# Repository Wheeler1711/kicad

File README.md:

# kicad
Jordan Wheeler PCBs files

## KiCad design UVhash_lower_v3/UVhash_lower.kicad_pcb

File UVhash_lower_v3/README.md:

## PCB file to make a breakout for 25 pin mico-D 

Also, there is DXF for a send cut send bracket to hold the PCB in the cyostat. Designed for 4-40 tapped holes

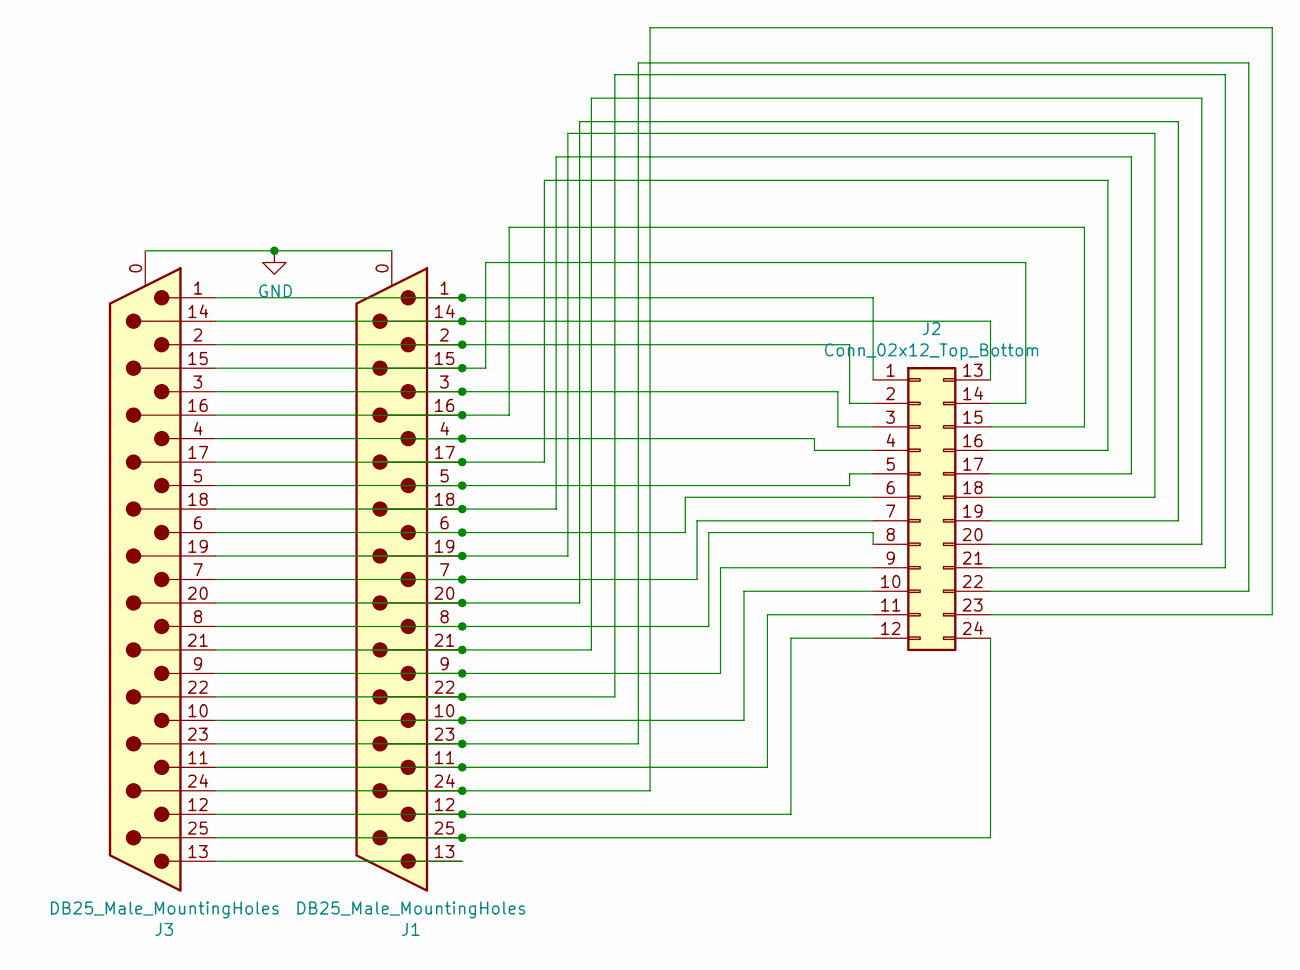
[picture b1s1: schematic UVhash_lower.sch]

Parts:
J1, J3: DB25_Male_MountingHoles; 25_pin_micro_D_male_straight_mount_pdb_wide_spacing
J2: Conn_02x12_Top_Bottom; PinSocket_2x12_P2.54mm_Vertical_twisted_pair

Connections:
GND: J1.0 (PAD), J3.0 (PAD)
unnamed: J1.1, J2.1, J3.1
unnamed: J1.2, J2.2, J3.2
unnamed: J1.3, J2.3, J3.3
unnamed: J1.4, J2.4, J3.4
unnamed: J1.5, J2.5, J3.5
unnamed: J1.6, J2.6, J3.6
unnamed: J1.7, J2.7, J3.7
unnamed: J1.8, J2.8, J3.8
unnamed: J1.9, J2.9, J3.9
unnamed: J1.10, J2.10, J3.10
unnamed: J1.11, J2.11, J3.11
unnamed: J1.12, J2.12, J3.12
unnamed: J1.13, J3.13
unnamed: J1.14, J2.13, J3.14
unnamed: J1.15, J2.14, J3.15
unnamed: J1.16, J2.15, J3.16
unnamed: J1.17, J2.16, J3.17
unnamed: J1.18, J2.17, J3.18
unnamed: J1.19, J2.18, J3.19
unnamed: J1.20, J2.19, J3.20
unnamed: J1.21, J2.20, J3.21
unnamed: J1.22, J2.21, J3.22
unnamed: J1.23, J2.22, J3.23
unnamed: J1.24, J2.23, J3.24
unnamed: J1.25, J2.24, J3.25

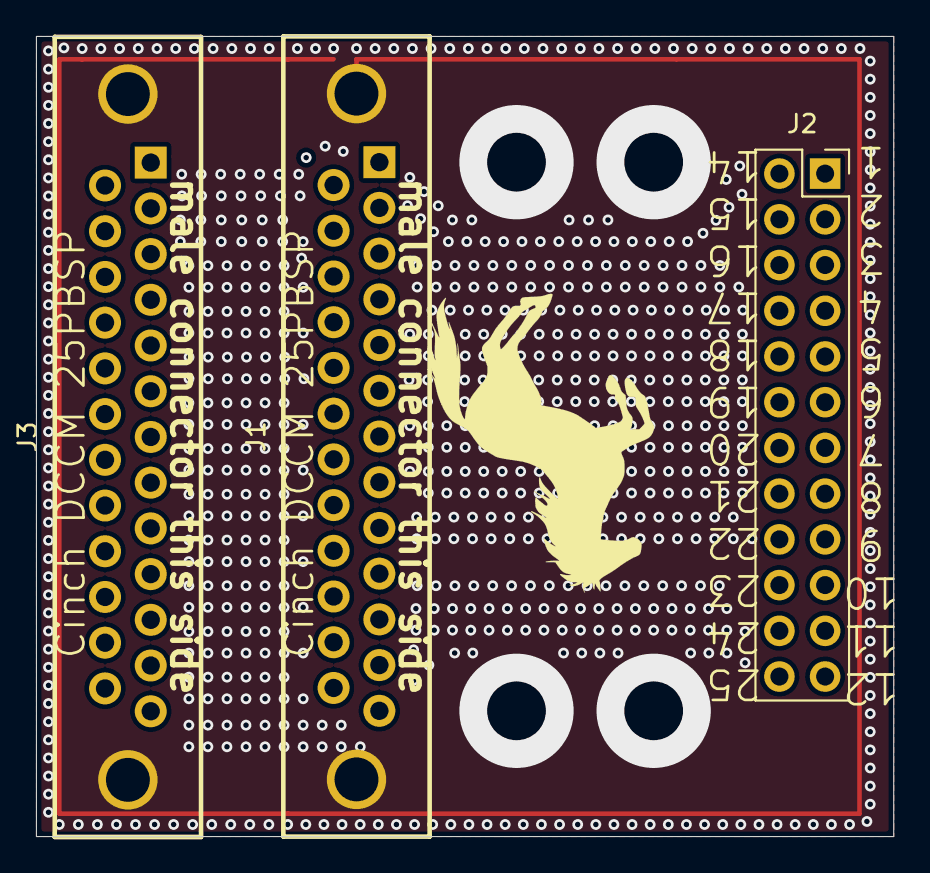
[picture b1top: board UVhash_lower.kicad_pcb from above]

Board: 4 copper layers, 47.6 x 44.5 mm, 3 parts (0 on the bottom side), 26 nets.

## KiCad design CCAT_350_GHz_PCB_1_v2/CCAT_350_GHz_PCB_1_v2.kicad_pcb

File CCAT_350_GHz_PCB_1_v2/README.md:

## PCB file for interface to 350 GHz CCAT arrays

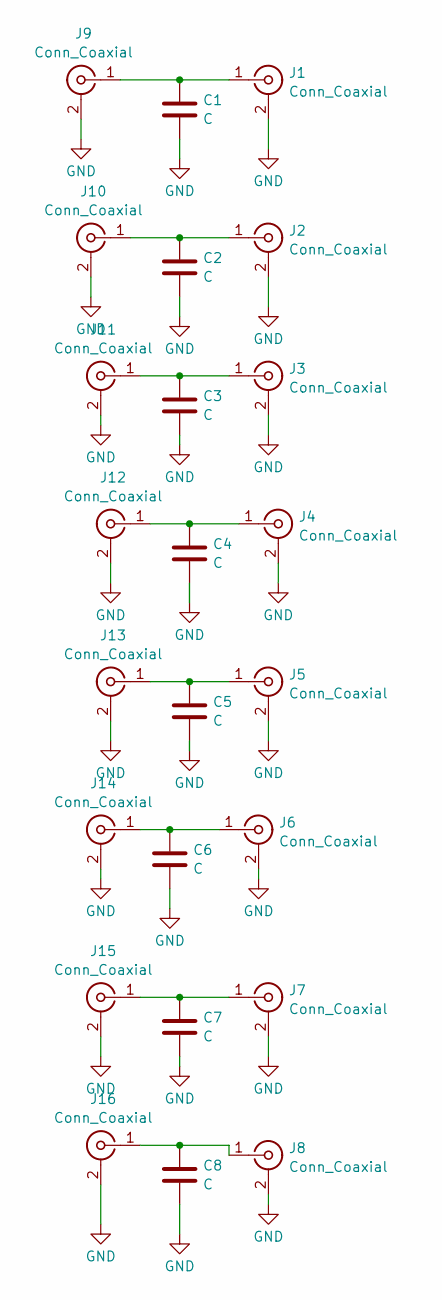
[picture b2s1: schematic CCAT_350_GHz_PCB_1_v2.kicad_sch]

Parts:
C1, C2, C3, C4, C5, C6, C7, C8: C; C_0402_1005Metric
J1, J2, J3, J4, J5, J6, J7, J8: Conn_Coaxial; coax_solder_cpw_44_trace_50_gap_rogers4350B_20_mil_thick
J9, J10, J11, J12, J13, J14, J15, J16: Conn_Coaxial; cpw_18_trace_4_gap_rogers_4350B_20_mil_thick

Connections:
GND: C1.2, C2.2, C3.2, C4.2, C5.2, C6.2, C7.2, C8.2, J1.2 (Ext), J2.2 (Ext), J3.2 (Ext), J4.2 (Ext), J5.2 (Ext), J6.2 (Ext), J7.2 (Ext), J8.2 (Ext), J9.2 (Ext), J10.2 (Ext), J11.2 (Ext), J12.2 (Ext), J13.2 (Ext), J14.2 (Ext), J15.2 (Ext), J16.2 (Ext)
unnamed: C1.1, J1.1 (In), J9.1 (In)
unnamed: C2.1, J2.1 (In), J10.1 (In)
unnamed: C3.1, J3.1 (In), J11.1 (In)
unnamed: C4.1, J4.1 (In), J12.1 (In)
unnamed: C5.1, J5.1 (In), J13.1 (In)
unnamed: C6.1, J6.1 (In), J14.1 (In)
unnamed: C7.1, J7.1 (In), J15.1 (In)
unnamed: C8.1, J8.1 (In), J16.1 (In)

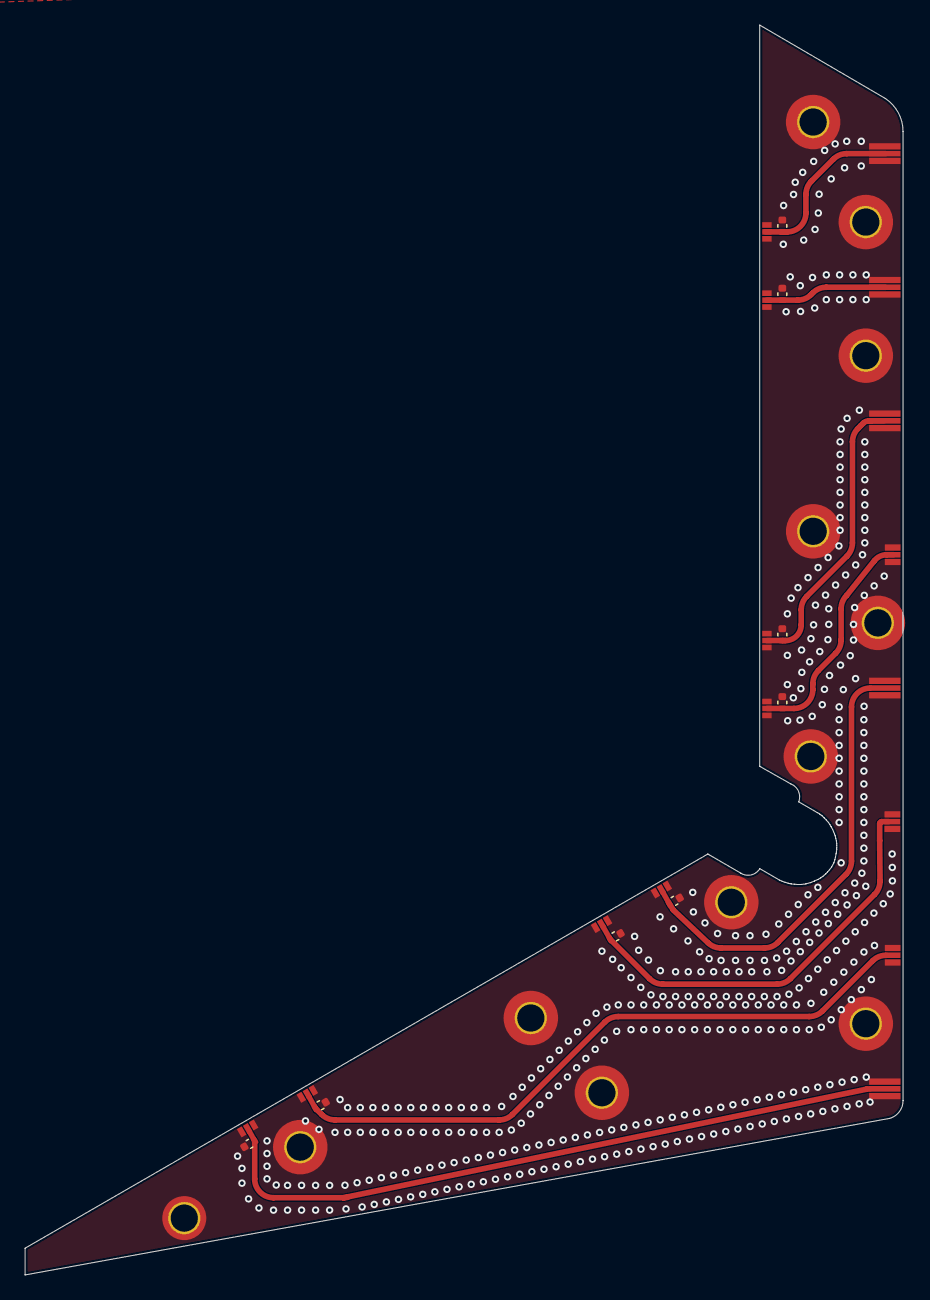
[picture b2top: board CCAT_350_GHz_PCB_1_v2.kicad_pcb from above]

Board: 2 copper layers, 70.9 x 101.0 mm, 24 parts (0 on the bottom side), 9 nets.

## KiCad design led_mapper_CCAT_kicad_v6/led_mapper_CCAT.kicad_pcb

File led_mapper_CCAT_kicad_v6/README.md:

## PCB file to led mapper for CCAT arrays

This is basically two arrays of charlieplexed leds

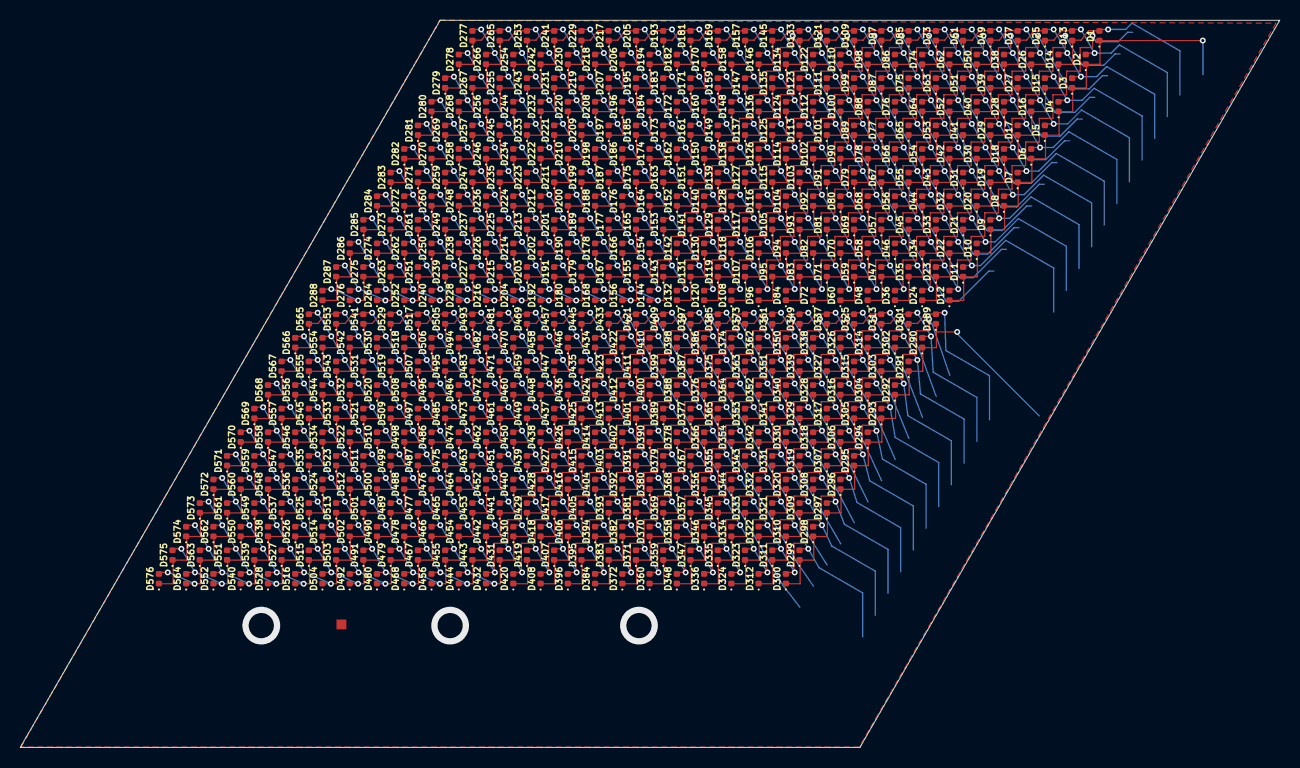
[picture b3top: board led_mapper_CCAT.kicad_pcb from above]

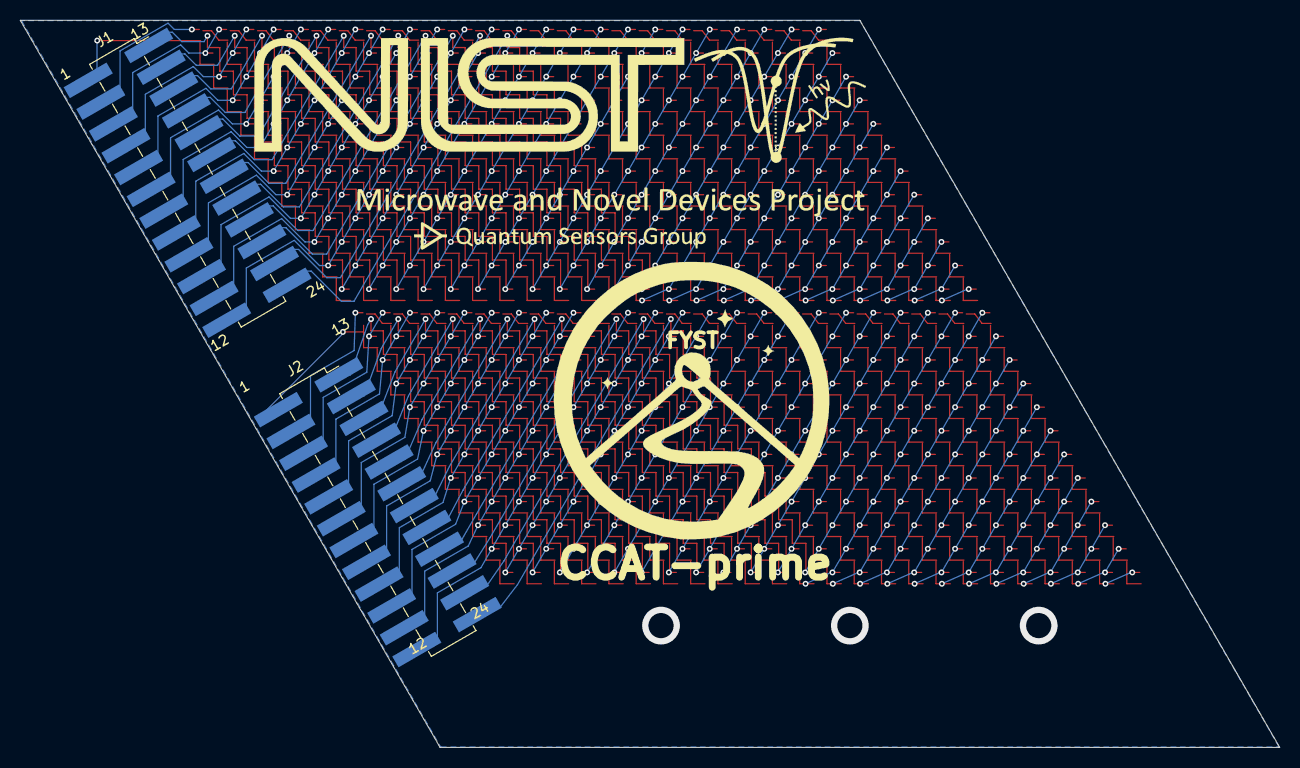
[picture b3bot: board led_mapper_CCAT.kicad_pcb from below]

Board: 2 copper layers, 127.0 x 73.4 mm, 579 parts (2 on the bottom side), 48 nets.

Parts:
D1, D2, D3, D4, D5, D6, D7, D8, D9, D10, D11, D12, D13, D14, D15, D16, D17, D18, D19, D20, D21, D22, D23, D24, D25, D26, D27, D28, D29, D30, D31, D32, D33, D34, D35, D36, D37, D38, D39, D40, D41, D42, D43, D44, D45, D46, D47, D48, D49, D50, D51, D52, D53, D54, D55, D56, D57, D58, D59, D60, D61, D62, D63, D64, D65, D66, D67, D68, D69, D70, D71, D72, D73, D74, D75, D76, D77, D78, D79, D80, D81, D82, D83, D84, D85, D86, D87, D88, D89, D90, D91, D92, D93, D94, D95, D96, D97, D98, D99, D100, D101, D102, D103, D104, D105, D106, D107, D108, D109, D110, D111, D112, D113, D114, D115, D116, D117, D118, D119, D120, D121, D122, D123, D124, D125, D126, D127, D128, D129, D130, D131, D132, D133, D134, D135, D136, D137, D138, D139, D140, D141, D142, D143, D144, D145, D146, D147, D148, D149, D150, D151, D152, D153, D154, D155, D156, D157, D158, D159, D160, D161, D162, D163, D164, D165, D166, D167, D168, D169, D170, D171, D172, D173, D174, D175, D176, D177, D178, D179, D180, D181, D182, D183, D184, D185, D186, D187, D188, D189, D190, D191, D192, D193, D194, D195, D196, D197, D198, D199, D200, D201, D202, D203, D204, D205, D206, D207, D208, D209, D210, D211, D212, D213, D214, D215, D216, D217, D218, D219, D220, D221, D222, D223, D224, D225, D226, D227, D228, D229, D230, D231, D232, D233, D234, D235, D236, D237, D238, D239, D240, D241, D242, D243, D244, D245, D246, D247, D248, D249, D250, D251, D252, D253, D254, D255, D256, D257, D258, D259, D260, D261, D262, D263, D264, D265, D266, D267, D268, D269, D270, D271, D272, D273, D274, D275, D276, D277, D278, D279, D280, D281, D282, D283, D284, D285, D286, D287, D288, D289, D290, D291, D292, D293, D294, D295, D296, D297, D298, D299, D300, D301, D302, D303, D304, D305, D306, D307, D308, D309, D310, D311, D312, D313, D314, D315, D316, D317, D318, D319, D320, D321, D322, D323, D324, D325, D326, D327, D328, D329, D330, D331, D332, D333, D334, D335, D336, D337, D338, D339, D340, D341, D342, D343, D344, D345, D346, D347, D348, D349, D350, D351, D352, D353, D354, D355, D356, D357, D358, D359, D360, D361, D362, D363, D364, D365, D366, D367, D368, D369, D370, D371, D372, D373, D374, D375, D376, D377, D378, D379, D380, D381, D382, D383, D384, D385, D386, D387, D388, D389, D390, D391, D392, D393, D394, D395, D396, D397, D398, D399, D400, D401, D402, D403, D404, D405, D406, D407, D408, D409, D410, D411, D412, D413, D414, D415, D416, D417, D418, D419, D420, D421, D422, D423, D424, D425, D426, D427, D428, D429, D430, D431, D432, D433, D434, D435, D436, D437, D438, D439, D440, D441, D442, D443, D444, D445, D446, D447, D448, D449, D450, D451, D452, D453, D454, D455, D456, D457, D458, D459, D460, D461, D462, D463, D464, D465, D466, D467, D468, D469, D470, D471, D472, D473, D474, D475, D476, D477, D478, D479, D480, D481, D482, D483, D484, D485, D486, D487, D488, D489, D490, D491, D492, D493, D494, D495, D496, D497, D498, D499, D500, D501, D502, D503, D504, D505, D506, D507, D508, D509, D510, D511, D512, D513, D514, D515, D516, D517, D518, D519, D520, D521, D522, D523, D524, D525, D526, D527, D528, D529, D530, D531, D532, D533, D534, D535, D536, D537, D538, D539, D540, D541, D542, D543, D544, D545, D546, D547, D548, D549, D550, D551, D552, D553, D554, D555, D556, D557, D558, D559, D560, D561, D562, D563, D564, D565, D566, D567, D568, D569, D570, D571, D572, D573, D574, D575, D576: LED; LED_0402_1005Metric
J1, J2: Conn_02x12_Top_Bottom; PinSocket_2x12_P2.54mm_Vertical_SMD_custom
J3: Conn_01x01_Female; TestPoint_Pad_1.0x1.0mm

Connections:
/pin1: D1.1, D2.1, D3.1, D4.1, D5.1, D6.1, D7.1, D8.1, D9.1, D10.1, D11.1, D12.1, J1.1
/pin1_b: D289.1, D290.1, D291.1, D292.1, D293.1, D294.1, D295.1, D296.1, D297.1, D298.1, D299.1, D300.1, J2.1
/pin2: D1.2, D13.1, D14.1, D15.1, D16.1, D17.1, D18.1, D19.1, D20.1, D21.1, D22.1, D23.1, D24.1, J1.2
/pin2_b: D289.2, D301.1, D302.1, D303.1, D304.1, D305.1, D306.1, D307.1, D308.1, D309.1, D310.1, D311.1, D312.1, J2.2
/pin3: D2.2, D13.2, D25.1, D26.1, D27.1, D28.1, D29.1, D30.1, D31.1, D32.1, D33.1, D34.1, D35.1, D36.1, J1.3
/pin3_b: D290.2, D301.2, D313.1, D314.1, D315.1, D316.1, D317.1, D318.1, D319.1, D320.1, D321.1, D322.1, D323.1, D324.1, J2.3
/pin4: D3.2, D14.2, D25.2, D37.1, D38.1, D39.1, D40.1, D41.1, D42.1, D43.1, D44.1, D45.1, D46.1, D47.1, D48.1, J1.4
/pin4_b: D291.2, D302.2, D313.2, D325.1, D326.1, D327.1, D328.1, D329.1, D330.1, D331.1, D332.1, D333.1, D334.1, D335.1, D336.1, J2.4
/pin5: D4.2, D15.2, D26.2, D37.2, D49.1, D50.1, D51.1, D52.1, D53.1, D54.1, D55.1, D56.1, D57.1, D58.1, D59.1, D60.1, J1.5
/pin5_b: D292.2, D303.2, D314.2, D325.2, D337.1, D338.1, D339.1, D340.1, D341.1, D342.1, D343.1, D344.1, D345.1, D346.1, D347.1, D348.1, J2.5
/pin6: D5.2, D16.2, D27.2, D38.2, D49.2, D61.1, D62.1, D63.1, D64.1, D65.1, D66.1, D67.1, D68.1, D69.1, D70.1, D71.1, D72.1, J1.6
/pin6_b: D293.2, D304.2, D315.2, D326.2, D337.2, D349.1, D350.1, D351.1, D352.1, D353.1, D354.1, D355.1, D356.1, D357.1, D358.1, D359.1, D360.1, J2.6
/pin7: D6.2, D17.2, D28.2, D39.2, D50.2, D61.2, D73.1, D74.1, D75.1, D76.1, D77.1, D78.1, D79.1, D80.1, D81.1, D82.1, D83.1, D84.1, J1.7
/pin7_b: D294.2, D305.2, D316.2, D327.2, D338.2, D349.2, D361.1, D362.1, D363.1, D364.1, D365.1, D366.1, D367.1, D368.1, D369.1, D370.1, D371.1, D372.1, J2.7
/pin8: D7.2, D18.2, D29.2, D40.2, D51.2, D62.2, D73.2, D85.1, D86.1, D87.1, D88.1, D89.1, D90.1, D91.1, D92.1, D93.1, D94.1, D95.1, D96.1, J1.8
/pin8_b: D295.2, D306.2, D317.2, D328.2, D339.2, D350.2, D361.2, D373.1, D374.1, D375.1, D376.1, D377.1, D378.1, D379.1, D380.1, D381.1, D382.1, D383.1, D384.1, J2.8
/pin9: D8.2, D19.2, D30.2, D41.2, D52.2, D63.2, D74.2, D85.2, D97.1, D98.1, D99.1, D100.1, D101.1, D102.1, D103.1, D104.1, D105.1, D106.1, D107.1, D108.1, J1.9
/pin9_b: D296.2, D307.2, D318.2, D329.2, D340.2, D351.2, D362.2, D373.2, D385.1, D386.1, D387.1, D388.1, D389.1, D390.1, D391.1, D392.1, D393.1, D394.1, D395.1, D396.1, J2.9
/pin10: D9.2, D20.2, D31.2, D42.2, D53.2, D64.2, D75.2, D86.2, D97.2, D109.1, D110.1, D111.1, D112.1, D113.1, D114.1, D115.1, D116.1, D117.1, D118.1, D119.1, D120.1, J1.10
/pin10_b: D297.2, D308.2, D319.2, D330.2, D341.2, D352.2, D363.2, D374.2, D385.2, D397.1, D398.1, D399.1, D400.1, D401.1, D402.1, D403.1, D404.1, D405.1, D406.1, D407.1, D408.1, J2.10
/pin11: D10.2, D21.2, D32.2, D43.2, D54.2, D65.2, D76.2, D87.2, D98.2, D109.2, D121.1, D122.1, D123.1, D124.1, D125.1, D126.1, D127.1, D128.1, D129.1, D130.1, D131.1, D132.1, J1.11
/pin11_b: D298.2, D309.2, D320.2, D331.2, D342.2, D353.2, D364.2, D375.2, D386.2, D397.2, D409.1, D410.1, D411.1, D412.1, D413.1, D414.1, D415.1, D416.1, D417.1, D418.1, D419.1, D420.1, J2.11
/pin12: D11.2, D22.2, D33.2, D44.2, D55.2, D66.2, D77.2, D88.2, D99.2, D110.2, D121.2, D133.1, D134.1, D135.1, D136.1, D137.1, D138.1, D139.1, D140.1, D141.1, D142.1, D143.1, D144.1, D156.2, D167.2, D178.2, D189.2, D200.2, D211.2, D222.2, D233.2, D244.2, D255.2, D266.2, D277.2, J1.12
/pin12_b: D299.2, D310.2, D321.2, D332.2, D343.2, D354.2, D365.2, D376.2, D387.2, D398.2, D409.2, D421.1, D422.1, D423.1, D424.1, D425.1, D426.1, D427.1, D428.1, D429.1, D430.1, D431.1, D432.1, D444.2, D455.2, D466.2, D477.2, D488.2, D499.2, D510.2, D521.2, D532.2, D543.2, D554.2, D565.2, J2.12
/pin13: D12.2, D23.2, D34.2, D45.2, D56.2, D67.2, D78.2, D89.2, D100.2, D111.2, D122.2, D133.2, D145.1, D146.1, D147.1, D148.1, D149.1, D150.1, D151.1, D152.1, D153.1, D154.1, D155.1, D156.1, D168.2, D179.2, D190.2, D201.2, D212.2, D223.2, D234.2, D245.2, D256.2, D267.2, D278.2, J1.13
/pin13_b: D300.2, D311.2, D322.2, D333.2, D344.2, D355.2, D366.2, D377.2, D388.2, D399.2, D410.2, D421.2, D433.1, D434.1, D435.1, D436.1, D437.1, D438.1, D439.1, D440.1, D441.1, D442.1, D443.1, D444.1, D456.2, D467.2, D478.2, D489.2, D500.2, D511.2, D522.2, D533.2, D544.2, D555.2, D566.2, J2.13
/pin14: D24.2, D35.2, D46.2, D57.2, D68.2, D79.2, D90.2, D101.2, D112.2, D123.2, D134.2, D145.2, D157.1, D158.1, D159.1, D160.1, D161.1, D162.1, D163.1, D164.1, D165.1, D166.1, D167.1, D168.1, D180.2, D191.2, D202.2, D213.2, D224.2, D235.2, D246.2, D257.2, D268.2, D279.2, J1.14
/pin14_b: D312.2, D323.2, D334.2, D345.2, D356.2, D367.2, D378.2, D389.2, D400.2, D411.2, D422.2, D433.2, D445.1, D446.1, D447.1, D448.1, D449.1, D450.1, D451.1, D452.1, D453.1, D454.1, D455.1, D456.1, D468.2, D479.2, D490.2, D501.2, D512.2, D523.2, D534.2, D545.2, D556.2, D567.2, J2.14
/pin15: D36.2, D47.2, D58.2, D69.2, D80.2, D91.2, D102.2, D113.2, D124.2, D135.2, D146.2, D157.2, D169.1, D170.1, D171.1, D172.1, D173.1, D174.1, D175.1, D176.1, D177.1, D178.1, D179.1, D180.1, D192.2, D203.2, D214.2, D225.2, D236.2, D247.2, D258.2, D269.2, D280.2, J1.15
/pin15_b: D324.2, D335.2, D346.2, D357.2, D368.2, D379.2, D390.2, D401.2, D412.2, D423.2, D434.2, D445.2, D457.1, D458.1, D459.1, D460.1, D461.1, D462.1, D463.1, D464.1, D465.1, D466.1, D467.1, D468.1, D480.2, D491.2, D502.2, D513.2, D524.2, D535.2, D546.2, D557.2, D568.2, J2.15
/pin16: D48.2, D59.2, D70.2, D81.2, D92.2, D103.2, D114.2, D125.2, D136.2, D147.2, D158.2, D169.2, D181.1, D182.1, D183.1, D184.1, D185.1, D186.1, D187.1, D188.1, D189.1, D190.1, D191.1, D192.1, D204.2, D215.2, D226.2, D237.2, D248.2, D259.2, D270.2, D281.2, J1.16
/pin16_b: D336.2, D347.2, D358.2, D369.2, D380.2, D391.2, D402.2, D413.2, D424.2, D435.2, D446.2, D457.2, D469.1, D470.1, D471.1, D472.1, D473.1, D474.1, D475.1, D476.1, D477.1, D478.1, D479.1, D480.1, D492.2, D503.2, D514.2, D525.2, D536.2, D547.2, D558.2, D569.2, J2.16
/pin17: D60.2, D71.2, D82.2, D93.2, D104.2, D115.2, D126.2, D137.2, D148.2, D159.2, D170.2, D181.2, D193.1, D194.1, D195.1, D196.1, D197.1, D198.1, D199.1, D200.1, D201.1, D202.1, D203.1, D204.1, D216.2, D227.2, D238.2, D249.2, D260.2, D271.2, D282.2, J1.17
/pin17_b: D348.2, D359.2, D370.2, D381.2, D392.2, D403.2, D414.2, D425.2, D436.2, D447.2, D458.2, D469.2, D481.1, D482.1, D483.1, D484.1, D485.1, D486.1, D487.1, D488.1, D489.1, D490.1, D491.1, D492.1, D504.2, D515.2, D526.2, D537.2, D548.2, D559.2, D570.2, J2.17
/pin18: D72.2, D83.2, D94.2, D105.2, D116.2, D127.2, D138.2, D149.2, D160.2, D171.2, D182.2, D193.2, D205.1, D206.1, D207.1, D208.1, D209.1, D210.1, D211.1, D212.1, D213.1, D214.1, D215.1, D216.1, D228.2, D239.2, D250.2, D261.2, D272.2, D283.2, J1.18
/pin18_b: D360.2, D371.2, D382.2, D393.2, D404.2, D415.2, D426.2, D437.2, D448.2, D459.2, D470.2, D481.2, D493.1, D494.1, D495.1, D496.1, D497.1, D498.1, D499.1, D500.1, D501.1, D502.1, D503.1, D504.1, D516.2, D527.2, D538.2, D549.2, D560.2, D571.2, J2.18
/pin19: D84.2, D95.2, D106.2, D117.2, D128.2, D139.2, D150.2, D161.2, D172.2, D183.2, D194.2, D205.2, D217.1, D218.1, D219.1, D220.1, D221.1, D222.1, D223.1, D224.1, D225.1, D226.1, D227.1, D228.1, D240.2, D251.2, D262.2, D273.2, D284.2, J1.19
/pin19_b: D372.2, D383.2, D394.2, D405.2, D416.2, D427.2, D438.2, D449.2, D460.2, D471.2, D482.2, D493.2, D505.1, D506.1, D507.1, D508.1, D509.1, D510.1, D511.1, D512.1, D513.1, D514.1, D515.1, D516.1, D528.2, D539.2, D550.2, D561.2, D572.2, J2.19
/pin20: D96.2, D107.2, D118.2, D129.2, D140.2, D151.2, D162.2, D173.2, D184.2, D195.2, D206.2, D217.2, D229.1, D230.1, D231.1, D232.1, D233.1, D234.1, D235.1, D236.1, D237.1, D238.1, D239.1, D240.1, D252.2, D263.2, D274.2, D285.2, J1.20
/pin20_b: D384.2, D395.2, D406.2, D417.2, D428.2, D439.2, D450.2, D461.2, D472.2, D483.2, D494.2, D505.2, D517.1, D518.1, D519.1, D520.1, D521.1, D522.1, D523.1, D524.1, D525.1, D526.1, D527.1, D528.1, D540.2, D551.2, D562.2, D573.2, J2.20
/pin21: D108.2, D119.2, D130.2, D141.2, D152.2, D163.2, D174.2, D185.2, D196.2, D207.2, D218.2, D229.2, D241.1, D242.1, D243.1, D244.1, D245.1, D246.1, D247.1, D248.1, D249.1, D250.1, D251.1, D252.1, D264.2, D275.2, D286.2, J1.21
/pin21_b: D396.2, D407.2, D418.2, D429.2, D440.2, D451.2, D462.2, D473.2, D484.2, D495.2, D506.2, D517.2, D529.1, D530.1, D531.1, D532.1, D533.1, D534.1, D535.1, D536.1, D537.1, D538.1, D539.1, D540.1, D552.2, D563.2, D574.2, J2.21
/pin22: D120.2, D131.2, D142.2, D153.2, D164.2, D175.2, D186.2, D197.2, D208.2, D219.2, D230.2, D241.2, D253.1, D254.1, D255.1, D256.1, D257.1, D258.1, D259.1, D260.1, D261.1, D262.1, D263.1, D264.1, D276.2, D287.2, J1.22
/pin22_b: D408.2, D419.2, D430.2, D441.2, D452.2, D463.2, D474.2, D485.2, D496.2, D507.2, D518.2, D529.2, D541.1, D542.1, D543.1, D544.1, D545.1, D546.1, D547.1, D548.1, D549.1, D550.1, D551.1, D552.1, D564.2, D575.2, J2.22
/pin23: D132.2, D143.2, D154.2, D165.2, D176.2, D187.2, D198.2, D209.2, D220.2, D231.2, D242.2, D253.2, D265.1, D266.1, D267.1, D268.1, D269.1, D270.1, D271.1, D272.1, D273.1, D274.1, D275.1, D276.1, D288.2, J1.23
/pin23_b: D420.2, D431.2, D442.2, D453.2, D464.2, D475.2, D486.2, D497.2, D508.2, D519.2, D530.2, D541.2, D553.1, D554.1, D555.1, D556.1, D557.1, D558.1, D559.1, D560.1, D561.1, D562.1, D563.1, D564.1, D576.2, J2.23
/pin24: D144.2, D155.2, D166.2, D177.2, D188.2, D199.2, D210.2, D221.2, D232.2, D243.2, D254.2, D265.2, D277.1, D278.1, D279.1, D280.1, D281.1, D282.1, D283.1, D284.1, D285.1, D286.1, D287.1, D288.1, J1.24
/pin24_b: D432.2, D443.2, D454.2, D465.2, D476.2, D487.2, D498.2, D509.2, D520.2, D531.2, D542.2, D553.2, D565.1, D566.1, D567.1, D568.1, D569.1, D570.1, D571.1, D572.1, D573.1, D574.1, D575.1, D576.1, J2.24

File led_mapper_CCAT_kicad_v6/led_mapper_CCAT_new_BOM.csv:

Comment,Designator,Footprint,LCSC
LED,"D1,D2,D3,D4,D5,D6,D7,D8,D9,D10,D11,D12,D13,D14,D15,D16,D17,D18,D19,D20,D21,D22,D23,D24,D25,D26,D27,D28,D29,D30,D31,D32,D33,D34,D35,D36,D37,D38,D39,D40,D41,D42,D43,D44,D45,D46,D47,D48,D49,D50,D51,D52,D53,D54,D55,D56,D57,D58,D59,D60,D61,D62,D63,D64,D65,D66,D67,D68,D69,D70,D71,D72,D73,D74,D75,D76,D77,D78,D79,D80,D81,D82,D83,D84,D85,D86,D87,D88,D89,D90,D91,D92,D93,D94,D95,D96,D97,D98,D99,D100,D101,D102,D103,D104,D105,D106,D107,D108,D109,D110,D111,D112,D113,D114,D115,D116,D117,D118,D119,D120,D121,D122,D123,D124,D125,D126,D127,D128,D129,D130,D131,D132,D133,D134,D135,D136,D137,D138,D139,D140,D141,D142,D143,D144,D145,D146,D147,D148,D149,D150,D151,D152,D153,D154,D155,D156,D157,D158,D159,D160,D161,D162,D163,D164,D165,D166,D167,D168,D169,D170,D171,D172,D173,D174,D175,D176,D177,D178,D179,D180,D181,D182,D183,D184,D185,D186,D187,D188,D189,D190,D191,D192,D193,D194,D195,D196,D197,D198,D199",LED_SMD:LED_0402_1005Metric,C409787
LED,"D200,D201,D202,D203,D204,D205,D206,D207,D208,D209,D210,D211,D212,D213,D214,D215,D216,D217,D218,D219,D220,D221,D222,D223,D224,D225,D226,D227,D228,D229,D230,D231,D232,D233,D234,D235,D236,D237,D238,D239,D240,D241,D242,D243,D244,D245,D246,D247,D248,D249,D250,D251,D252,D253,D254,D255,D256,D257,D258,D259,D260,D261,D262,D263,D264,D265,D266,D267,D268,D269,D270,D271,D272,D273,D274,D275,D276,D277,D278,D279,D280,D281,D282,D283,D284,D285,D286,D287,D288,D289,D290,D291,D292,D293,D294,D295,D296,D297,D298,D299,D300,D301,D302,D303,D304,D305,D306,D307,D308,D309,D310,D311,D312,D313,D314,D315,D316,D317,D318,D319,D320,D321,D322,D323,D324,D325,D326,D327,D328,D329,D330,D331,D332,D333,D334,D335,D336,D337,D338,D339,D340,D341,D342,D343,D344,D345,D346,D347,D348,D349,D350,D351,D352,D353,D354,D355,D356,D357,D358,D359,D360,D361,D362,D363,D364,D365,D366,D367,D368,D369,D370,D371,D372,D373,D374,D375,D376,D377,D378,D379,D380,D381,D382,D383,D384,D385,D386,D387,D388,D389,D390,D391,D392,D393,D394,D395,D396,D397,D398,D399",LED_SMD:LED_0402_1005Metric,C409787
LED,"D400,D401,D402,D403,D404,D405,D406,D407,D408,D409,D410,D411,D412,D413,D414,D415,D416,D417,D418,D419,D420,D421,D422,D423,D424,D425,D426,D427,D428,D429,D430,D431,D432,D433,D434,D435,D436,D437,D438,D439,D440,D441,D442,D443,D444,D445,D446,D447,D448,D449,D450,D451,D452,D453,D454,D455,D456,D457,D458,D459,D460,D461,D462,D463,D464,D465,D466,D467,D468,D469,D470,D471,D472,D473,D474,D475,D476,D477,D478,D479,D480,D481,D482,D483,D484,D485,D486,D487,D488,D489,D490,D491,D492,D493,D494,D495,D496,D497,D498,D499,D500,D501,D502,D503,D504,D505,D506,D507,D508,D509,D510,D511,D512,D513,D514,D515,D516,D517,D518,D519,D520,D521,D522,D523,D524,D525,D526,D527,D528,D529,D530,D531,D532,D533,D534,D535,D536,D537,D538,D539,D540,D541,D542,D543,D544,D545,D546,D547,D548,D549,D550,D551,D552,D553,D554,D555,D556,D557,D558,D559,D560,D561,D562,D563,D564,D565,D566,D567,D568,D569,D570,D571,D572,D573,D574,D575,D576",LED_SMD:LED_0402_1005Metric,C409787
Conn_02x12_Top_Bottom,"J1,J2",rectangular_custom:PinSocket_2x12_P2.54mm_Vertical_SMD_custom,
Conn_01x01_Female,J3,TestPoint:TestPoint_Pad_1.0x1.0mm,

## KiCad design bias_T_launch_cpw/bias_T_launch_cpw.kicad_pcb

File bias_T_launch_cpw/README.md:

## PCB file to make a bias T cpw launch for mini circuits TCBT-123+

intended for 20 mil thick Rogers-RO4350B

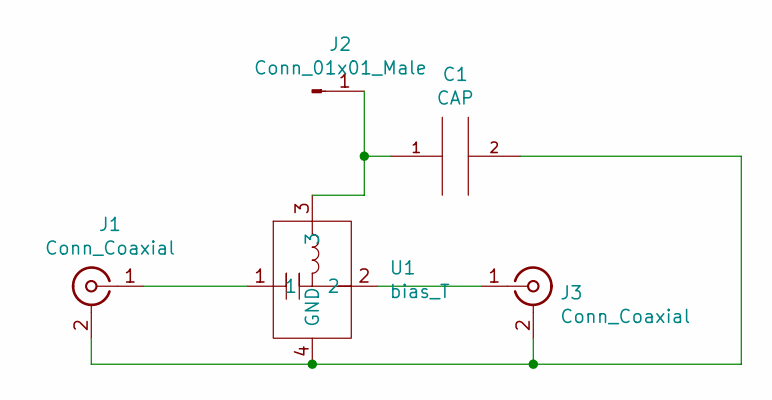
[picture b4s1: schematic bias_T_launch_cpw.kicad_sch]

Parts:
C1: CAP; C_0603_1608Metric
J1: Conn_Coaxial; 44mil_microstrip
J2: Conn_01x01_Male; PinHeader_1x01_P2.54mm_Vertical
J3: Conn_Coaxial; cpw_31_trace_16p5_gap
U1: bias_T; mini_circuits_gu1414

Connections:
unnamed: C1.1, J2.1, U1.3
unnamed: C1.2, J1.2 (Ext), J3.2 (Ext), U1.4 (GND)
unnamed: J1.1 (In), U1.1
unnamed: J3.1 (In), U1.2

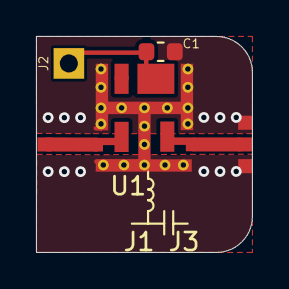
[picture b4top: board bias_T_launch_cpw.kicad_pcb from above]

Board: 2 copper layers, 12.0 x 12.0 mm, 5 parts (1 on the bottom side), 4 nets.

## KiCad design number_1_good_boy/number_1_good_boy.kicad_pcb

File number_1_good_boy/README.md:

# PCB file to make an LED chaser dog tag for any number 1 good doggo.
## Below is what the final product ended up looking like.

One day my number 1 good boy, through no fault of his own, lost all of his doggo tags. So naturally, instead of simply buying him a new dog tag at minimal cost and effort, I decided to make a special dog tag for my special boy so that everyone would know just how special he is. I mean just look at how cute he is at the park...

or in the sand.

Anyway, resisting the urge to post a thousand good boy pictures... I decided I wanted some blinking LEDs and after a bit of googling ended up deciding on an LED chaser circuit e.g. [Nuts and Volts](https://www.nutsvolts.com/magazine/article/led-chaser-sequencer-circuits) or [Electro Schematics](https://www.electroschematics.com/led-chaser/).

Then I set out to design this circuit in [KiCad](https://kicad.org/) (my favorite PCB design software). 
Before designing the schematic I decided on what ICs I was going to use. Basically, I knew that I wanted to try JLCPCB's SMT assembly service. Mostly because an SMD versus a through-hole PCB would look slicker in my opinion. Also, it was a good opportunity to learn how to specify an SMD board. JLCPCB also is very affordable which made such a project possible with a modest budget (still not the cheapest dog tag in the end). So I picked out a 555 timer and a CMOS decade counter that were in JLCPCB SMT [library](https://jlcpcb.com/parts) and in stock. In particular, the [NE555](http://www.ti.com/lit/ds/symlink/ne555.pdf) and the [CD4017BM96](https://datasheet.lcsc.com/szlcsc/1809042113_Texas-Instruments-CD4017BM96_C11349.pdf). The CD4017BM96 stated it would work down to 3V which was what I needed to run the LED chaser off a battery. Likewise, I made sure the LED would run off a voltage of ~3V [NCD0603W3](https://datasheet.lcsc.com/szlcsc/2008201033_Foshan-NationStar-Optoelectronics-NCD0603W3_C158100.pdf).

I wired up the 555 timer in the schematic for a stable operation as shown on page 11 of the datasheet. You set the rate of the LED chaser by setting the values of  R<sub>A</sub>, R<sub>B</sub>, and C. I used an online [calculator](https://www.xarg.org/tools/ne555-astable-circuit-calculator/) to choose the component values to obtain a rate of ~6 Hz. Then I wired the output of the 555 timer into the clock input of the CD4017B. Then I just added an LED to each of the output pins of the CD4017B. Since the battery will just supply 3V there was no need for any current limiting resistors in series with the LEDs. Then I just added in a [switch](https://lcsc.com/product-detail/New-Arrivals_XKB-Enterprise-SK-3296S-01-L2_C500051.html) and a battery into the circuit. For the battery, I chose an SMD part that was already in the KiCad footprint library. JLCPCB didn't stock it but the battery needed to go on the back anyway and JLCPCB only does SMD assembly on one side. Below is my schematic. 

There are good tutorials already out there on how to use KiCad ([check out SparkFun's](https://learn.sparkfun.com/tutorials/beginners-guide-to-kicad)) so I won't go into too much detail on that part of the project. However, when assigning footprints KiCad had all of the footprints I needed for my SMD components except for the [switch](https://lcsc.com/product-detail/New-Arrivals_XKB-Enterprise-SK-3296S-01-L2_C500051.html). I had to draw up a new footprint for that part from the diagram in the datasheet. You can find it in this same repository [here](https://github.com/Wheeler1711/kicad/tree/main/my_footprints/switch.pretty). Picture below.

My good boy needed a new tag soon so that he didn't wander off and get lost, so I didn't spend too much time making the prettiest PCB or fanciest design. Your version could be in the shape of a dog bone! I did a bit of quick math to place the LEDs evenly around the circle (see the excel file in the repository) and wired everything up. Below is a picture of the PCB after I had everything wired up. 

I didn't wire up any of the grounds, I just let the ground pour accomplish that for me. Below shows what it looked like after the ground pour.

Finally, the 3D rendering from KiCad is shown below without the switch which I didn't bother making a 3D model for.  

I used the instructions [here](https://support.jlcpcb.com/article/84-how-to-generate-the-bom-and-centroid-file-from-kicad) to create the BOM and position file needed for the JLCPCB software to do the SMD assembly. After uploading the files to JLCPCB's website, their preview showed that the IC's rotation angles were off by 90 degrees so I just manually edited the top-pos.csv file by subtracting 90 degrees and re-uploaded. The version in this repository is the corrected version. 

If you want to make one for yourself just download the project. Open the PCB design in PCBnew and change the text on the front silkscreen to have your doggo's name and numbers. Then go to File->Plot. Make sure the plot format is set to Gerber, then hit Plot. Also, click Generate Drill Files... under the same plot pop-up and then click Generate Drill File. Then you just need to zip all of the .gbr and .drl files and upload that file through JLCPCB's website. Next, when prompted, upload the BOM and top-pos.csv file. If you haven't changed the circuit, the current versions should work just fine. The JLCPCB website gives you previews of the board and the SMD components so you should notice if something is amiss.

I chose a black PCB because it was prettier than green and a blue PCB required me to get qty 30 instead of a min quantity of 5 which would have brought the price up ~$20. In the end with a 7 dollar off coupon for SMT assembly the board cost me $18.46 with an additional $17.80 for the shipping. Part of the cost is from some of the parts being from the extended part library which triggered a 9 dollar fee ($3 for LEDs, $3 for the switch, and $3 for the CD4017B), however, since all of the CD4017Bs and all of the toggle switches are in the extended library you can't avoid that. There are 0804 LEDs that are basic parts though. In the end, I would have been better off in terms of budget to just have purchased a regular dog tag but would have had much less fun. 

Finally, I also need the SMD [part](https://www.digikey.com/en/products/detail/keystone-electronics/1058/5255484) for the battery which I bought from Digikey along with some [batteries](https://www.digikey.com/en/products/detail/panasonic-bsg/CR2032/31939) as well. 5 holders and 5 batteries came out at 6.70 but then I paid another $15 in shipping. If you are clever you might avoid the shipping charges by finding a local supplier of the battery holder component and of course you can buy the batteries from lots of different stores. 

A couple weeks later my PCBs arrived and I just had to quickly solder on the battery holder which given the large contacts was no trouble at all.

To my surprise, the board worked right out of the box (not the usual situation for many of my projects). Since the board doesn't have any microcontrollers there is no need to program anything and it just works right away. Of course, if you made a tag with a microcontroller you would be able to program in new LED patterns. The final product is shown at the very top of the page. And below is a picture of my #1 good boy showing off his new bling. Warning this is not recommended for good doggo's who might be tempted to eat batteries. I leave the battery out when it is not in use.

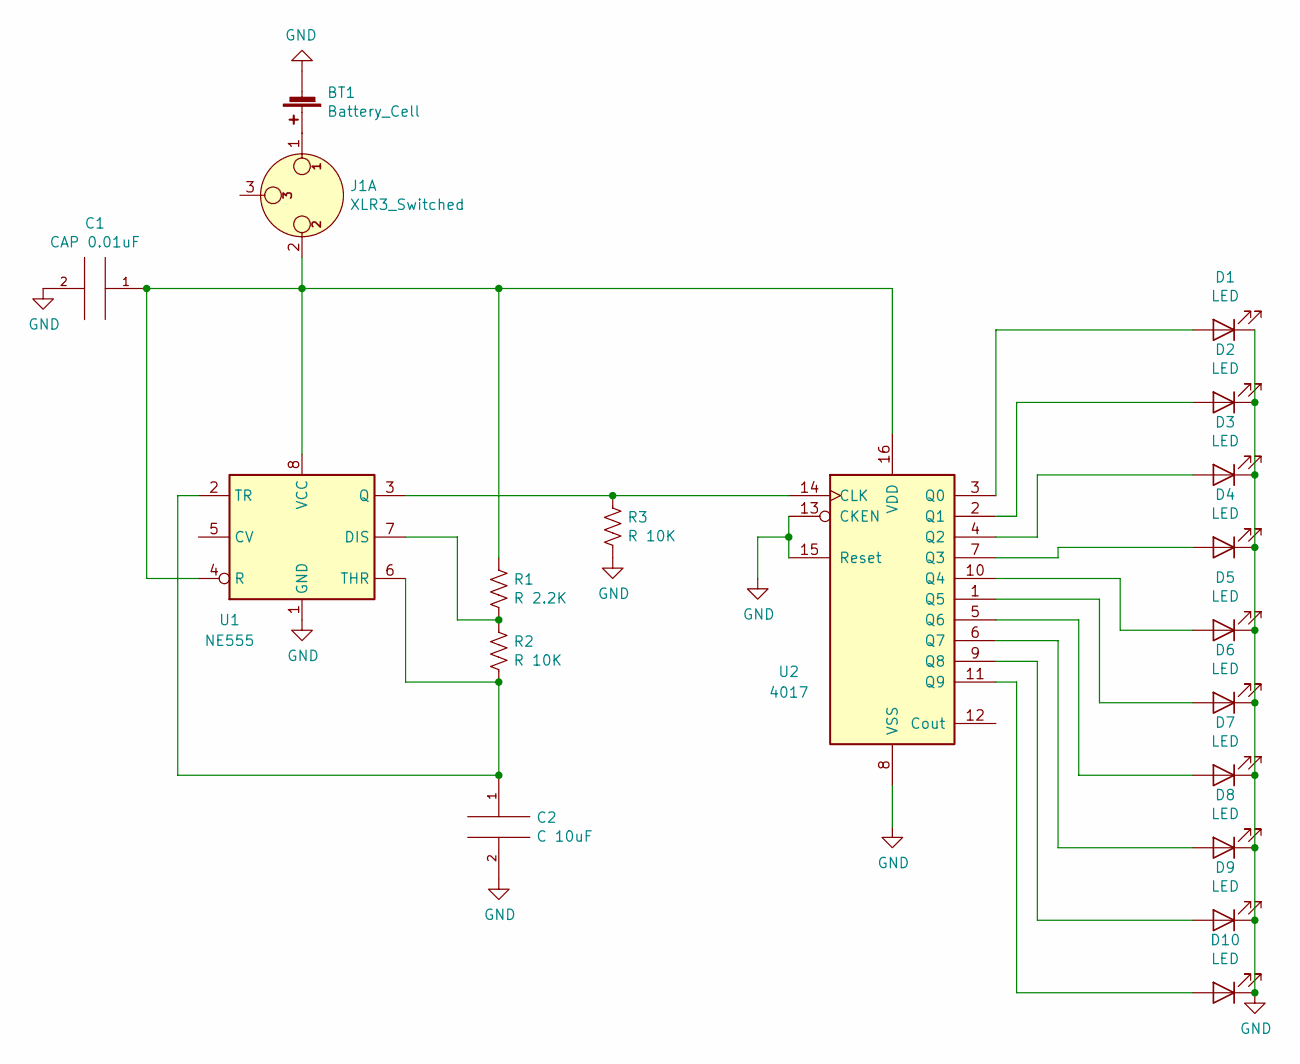
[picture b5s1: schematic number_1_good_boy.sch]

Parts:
BT1: Battery_Cell; BatteryHolder_Keystone_1058_1x2032
C1: CAP 0.01uF; C_0603_1608Metric; LCSC C57112
C2: C 10uF; C_0603_1608Metric; LCSC C19702
D1, D2, D3, D4, D5, D6, D7, D8, D9, D10: LED; LED_0603_1608Metric; LCSC C158100
J1: XLR3_Switched; surface_mount_switch_SK-3296S-01-L2; LCSC C500051
R1: R 2.2K; R_0603_1608Metric; LCSC C4190
R2, R3: R 10K; R_0603_1608Metric; LCSC C25804
U1: NE555; SOIC-8_3.9x4.9mm_P1.27mm; LCSC C7593
U2: 4017; SOIC-16_3.9x9.9mm_P1.27mm; LCSC C11349

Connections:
GND: BT1.2 (-), C1.2, C2.2, D1.1 (K), D2.1 (K), D3.1 (K), D4.1 (K), D5.1 (K), D6.1 (K), D7.1 (K), D8.1 (K), D9.1 (K), D10.1 (K), R3.2, U1.1 (GND), U2.8 (VSS), U2.13 (CKEN), U2.15 (Reset)
unnamed: BT1.1 (+), J1.1
unnamed: C1.1, J1.2, R1.1, U1.4 (R), U1.8 (VCC), U2.16 (VDD)
unnamed: C2.1, R2.2, U1.2 (TR), U1.6 (THR)
unnamed: D1.2 (A), U2.3 (Q0)
unnamed: D2.2 (A), U2.2 (Q1)
unnamed: D3.2 (A), U2.4 (Q2)
unnamed: D4.2 (A), U2.7 (Q3)
unnamed: D5.2 (A), U2.10 (Q4)
unnamed: D6.2 (A), U2.1 (Q5)
unnamed: D7.2 (A), U2.5 (Q6)
unnamed: D8.2 (A), U2.6 (Q7)
unnamed: D9.2 (A), U2.9 (Q8)
unnamed: D10.2 (A), U2.11 (Q9)
unnamed: R1.2, R2.1, U1.7 (DIS)
unnamed: R3.1, U1.3 (Q), U2.14 (CLK)
